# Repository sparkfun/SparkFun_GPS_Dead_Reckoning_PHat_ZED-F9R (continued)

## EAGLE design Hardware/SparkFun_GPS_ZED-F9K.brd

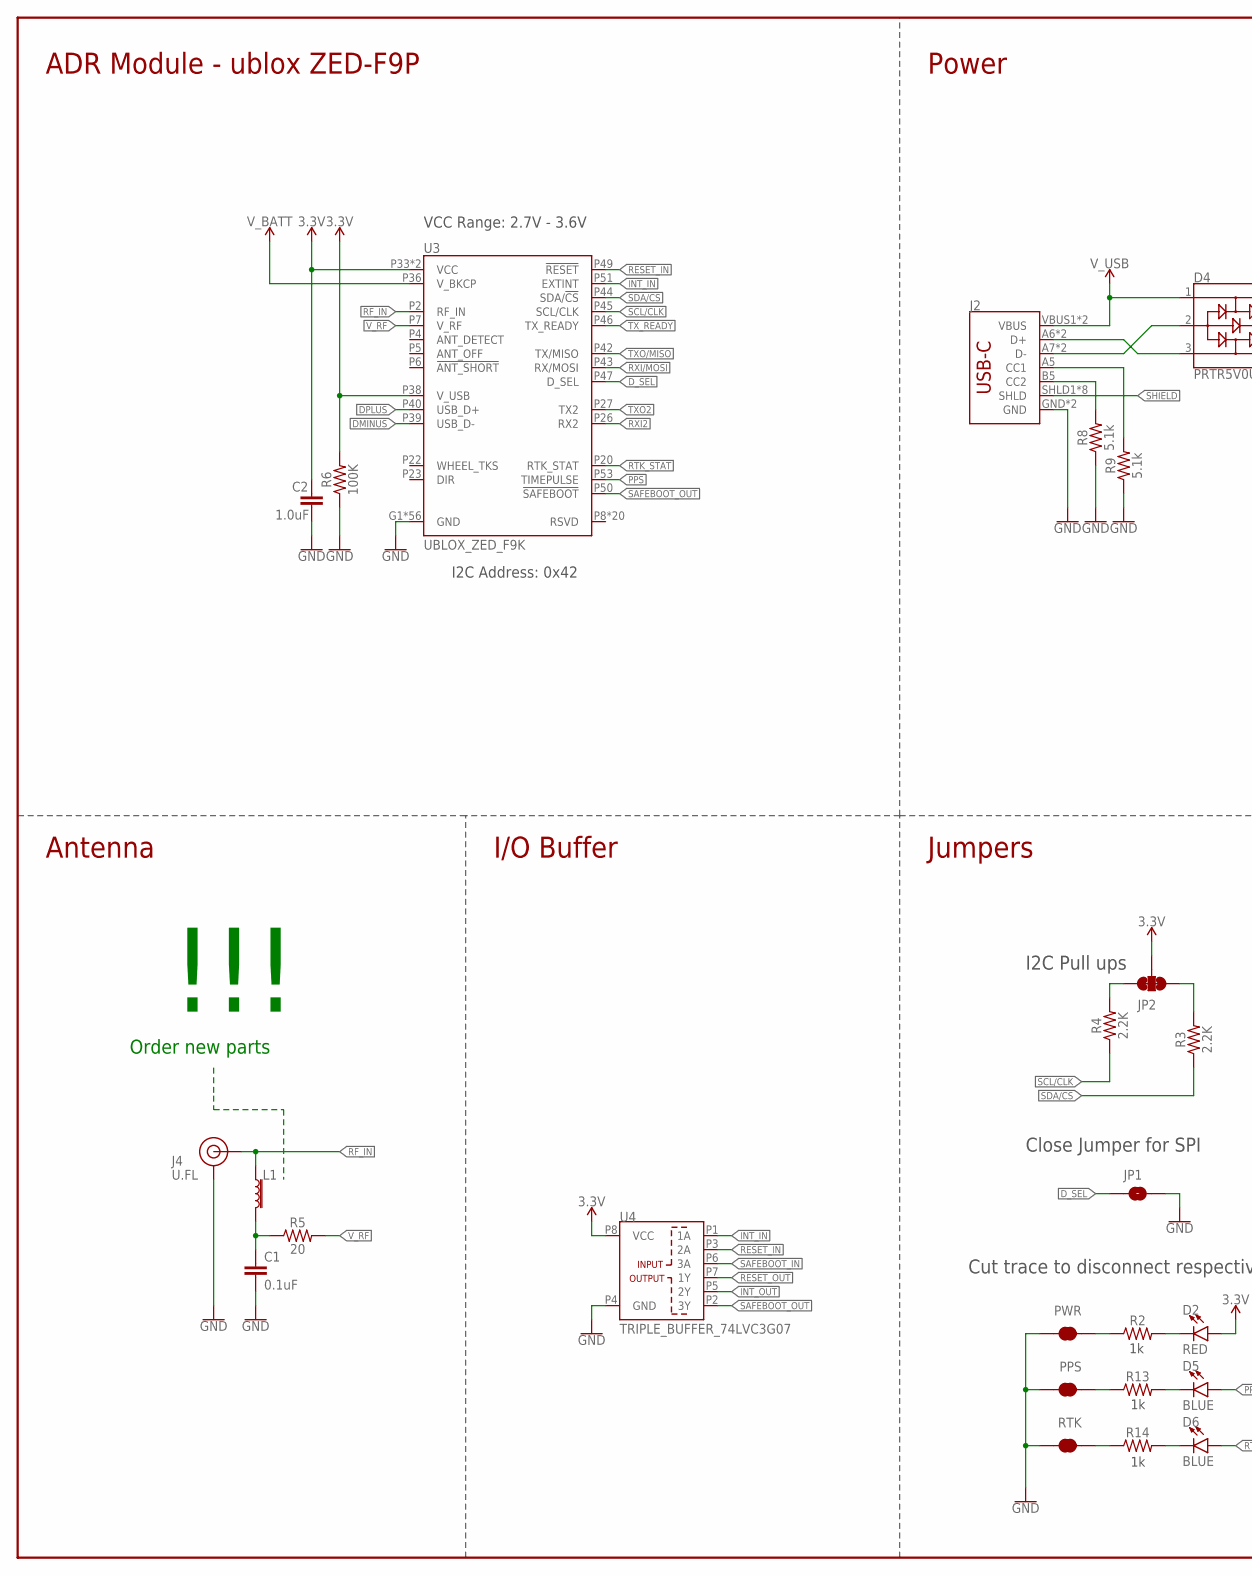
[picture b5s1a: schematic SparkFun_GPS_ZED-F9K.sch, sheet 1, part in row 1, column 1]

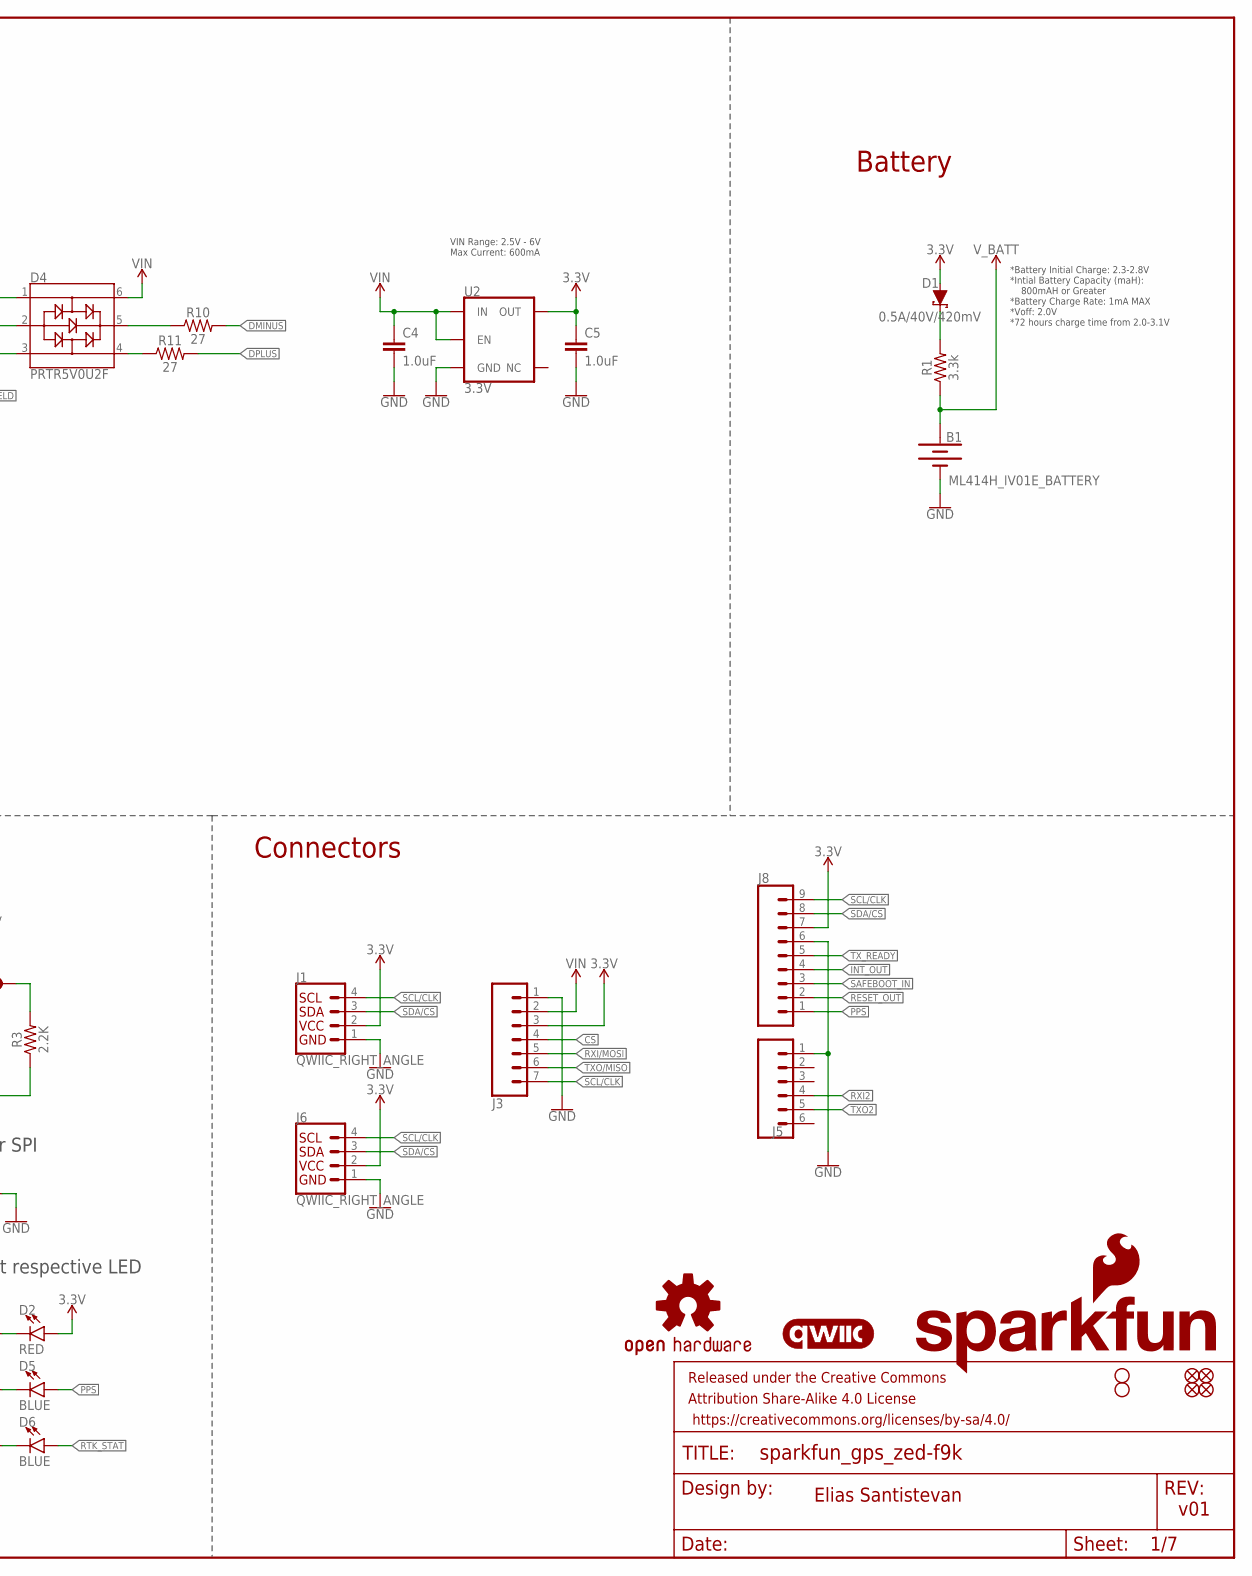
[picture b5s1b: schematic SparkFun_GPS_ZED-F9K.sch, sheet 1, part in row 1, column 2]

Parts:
B1: ML414H_IV01E_BATTERY; ML414H_IV01E
C1: 0.1uF; 0402
C2: 1.0uF; 0402
C4, C5: 1.0uF; 0603
D1: 0.5A/40V/420mV; SOD-323
D2: RED; LED-0603
D4: PRTR5V0U2F; SOT886
D5, D6: BLUE; LED-0603
FD1, FD2, FD3, FD4: FIDUCIALUFIDUCIAL; FIDUCIAL-MICRO
FRAME2: FRAME-LEDGER; CREATIVE_COMMONS
H2, H3: STAND-OFFTIGHT; STAND-OFF-TIGHT
J1, J6: QWIIC_RIGHT_ANGLE; JST04_1MM_RA
J2: USB_C2-LAYER; USB-C-16P
J3: CONN_07NO_SILK; 1X07_NO_SILK
J4: U.FL
J5: CONN_06NO_SILK_NO_POP; 1X06_NO_SILK
J8: CONN_09NO_SILK; 1X09_NO_SILK
JP1: JUMPER-SMT_2_NO_SILK; SMT-JUMPER_2_NO_SILK
JP2: JUMPER-SMT_3_2-NC_TRACE_SILK; SMT-JUMPER_3_2-NC_TRACE_SILK
L1: 3.9NH; 0402
LOGO1: SFE_LOGO_NAME_FLAME.2_INCH; SFE_LOGO_NAME_FLAME_.2
LOGO2: QWIIC_LOGO_4MM; QWIIC_4MM
LOGO3: OSHW-LOGOM; OSHW-LOGO-M
PPS: JUMPER-SMT_2_NC_TRACE_SILK; SMT-JUMPER_2_NC_TRACE_SILK
PWR: JUMPER-SMT_2_NC_TRACE_SILK; SMT-JUMPER_2_NC_TRACE_SILK
R1: 3.3k; 0603
R2, R13, R14: 1KOHM-0402-1/16W-1%; 0402
R3, R4: 2.2K; 0402
R5: 20; 0603
R6: 100K; 0402
R8, R9: 5.1k; 0402
R10, R11: 27; 0603
RTK: JUMPER-SMT_2_NC_TRACE_SILK; SMT-JUMPER_2_NC_TRACE_SILK
U2: 3.3V; SOT23-5
U3: UBLOX_ZED_F9K
U4: TRIPLE_BUFFER_74LVC3G07; SOP_8-PIN

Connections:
3.3V: C2.1, C5.1, D1.A, D2.A, J1.2, J3.3, J6.2, J8.7, JP2.2, R6.2, U2.5 (OUT), U3.P33 (VCC), U3.P34 (VCC), U3.P38 (V_USB), U4.P8 (VCC)
!CS: J3.4
!RESET_IN: U3.P49 (!RESET!), U4.P3 (2A)
!RESET_OUT: J8.2, U4.P7 (1Y)
!SAFEBOOT_IN: J8.3, U4.P6 (3A)
!SAFEBOOT_OUT: U3.P50 (!SAFEBOOT!), U4.P2 (3Y)
DMINUS: R10.2, U3.P39 (USB_D-)
DPLUS: R11.2, U3.P40 (USB_D+)
D_SEL: JP1.1, U3.P47 (D_SEL)
GND: B1.-, C1.2, C2.2, C4.2, C5.2, J1.1, J2.GND, J2.GND2 (GND), J3.1, J4.1 (GND), J4.2 (GND), J5.1, J6.1, J8.6, JP1.2, PPS.1, PWR.1, R6.1, R8.1, R9.1, RTK.1, U2.2 (GND), U3.G1 (GND), U3.G2 (GND), U3.G3 (GND), U3.G4 (GND), U3.G5 (GND), U3.G6 (GND), U3.G7 (GND), U3.G8 (GND), U3.G9 (GND), U3.G10 (GND), U3.G11 (GND), U3.G12 (GND), U3.G13 (GND), U3.G14 (GND), U3.G15 (GND), U3.G16 (GND), U3.G17 (GND), U3.G18 (GND), U3.G19 (GND), U3.G20 (GND), U3.G21 (GND), U3.G22 (GND), U3.G23 (GND), U3.G24 (GND), U3.G25 (GND), U3.G26 (GND), U3.G27 (GND), U3.G28 (GND), U3.G29 (GND), U3.G30 (GND), U3.G31 (GND), U3.G32 (GND), U3.G33 (GND), U3.G34 (GND), U3.G35 (GND), U3.G36 (GND), U3.G37 (GND), U3.G38 (GND), U3.G39 (GND), U3.G40 (GND), U3.G41 (GND), U3.G42 (GND), U3.G43 (GND), U3.G44 (GND), U3.G45 (GND), U3.G46 (GND), U3.G47 (GND), U3.G48 (GND), U3.P1 (GND), U3.P3 (GND), U3.P12 (GND), U3.P14 (GND), U3.P32 (GND), U3.P37 (GND), U3.P41 (GND), U3.P48 (GND), U4.P4 (GND)
INT_IN: U3.P51 (EXTINT), U4.P1 (1A)
INT_OUT: J8.4, U4.P5 (2Y)
unnamed: JP2.1, R3.2
unnamed: D1.C, R1.2
unnamed: JP2.3, R4.2
unnamed: D2.C, R2.2
unnamed: C1.1, L1.2, R5.1
unnamed: D4.3, J2.A6 (D+), J2.B6 (D+)
unnamed: D4.2, J2.A7 (D-), J2.B7 (D-)
unnamed: PWR.2, R2.1
unnamed: J2.B5 (CC2), R8.2
unnamed: J2.A5 (CC1), R9.2
unnamed: D4.5, R10.1
unnamed: D4.4, R11.1
unnamed: R14.1, RTK.2
unnamed: PPS.2, R13.1
unnamed: D5.C, R13.2
unnamed: D6.C, R14.2
PPS: D5.A, J8.1, U3.P53 (TIMEPULSE)
RF_IN: J4.FEED (SIGNAL), L1.1, U3.P2 (RF_IN)
RTK_STAT: D6.A, U3.P20 (RTK_STAT)
RXI2: J5.4, U3.P26 (RX2)
RXI/MOSI: J3.5, U3.P43 (RX/MOSI)
SCL/CLK: J1.4, J3.7, J6.4, J8.9, R4.1, U3.P45 (SCL/CLK)
SDA/!CS: J1.3, J6.3, J8.8, R3.1, U3.P44 (SDA/!CS!)
SHIELD: J2.SHLD1 (SHLD), J2.SHLD2 (SHLD), J2.SHLD3 (SHLD), J2.SHLD4 (SHLD), J2.SHLD5 (SHLD), J2.SHLD6 (SHLD), J2.SHLD7 (SHLD), J2.SHLD8 (SHLD)
TXO2: J5.5, U3.P27 (TX2)
TXO/MISO: J3.6, U3.P42 (TX/MISO)
TX_READY: J8.5, U3.P46 (TX_READY)
VIN: C4.1, D4.6, J3.2, U2.1 (IN), U2.3 (EN)
V_BATT: B1.+, R1.1, U3.P36 (V_BKCP)
V_RF: R5.2, U3.P7 (V_RF)
V_USB: D4.1, J2.VBUS1 (VBUS), J2.VBUS2 (VBUS)

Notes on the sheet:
v01
Elias Santistevan
ADR Module - ublox ZED-F9P
Battery
Connectors
Jumpers
Close Jumper for SPI
I2C Pull ups
Cut trace to disconnect respective LED
Antenna
*Battery Initial Charge: 2.3-2.8V *Intial Battery Capacity (maH): 800mAH or Greater *Battery Charge Rate: 1mA MAX *Voff: 2.0V *72 hours charge time from 2.0-3.1V
Order new parts
!!!
VIN Range: 2.5V - 6V Max Current: 600mA
Power
I/O Buffer
VCC Range: 2.7V - 3.6V
I2C Address: 0x42

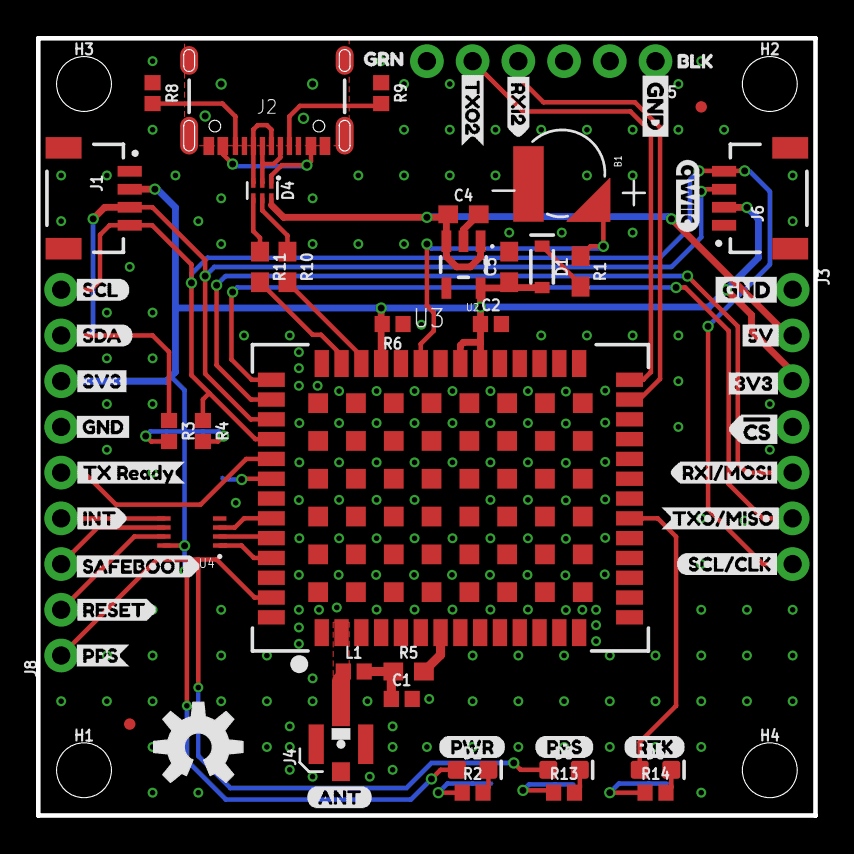
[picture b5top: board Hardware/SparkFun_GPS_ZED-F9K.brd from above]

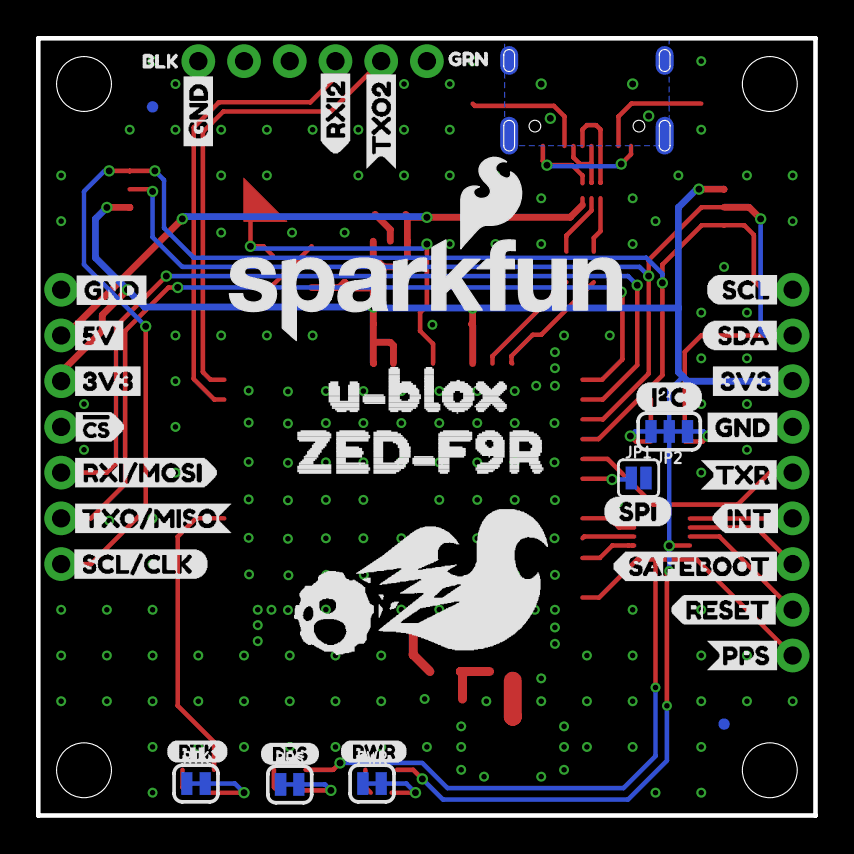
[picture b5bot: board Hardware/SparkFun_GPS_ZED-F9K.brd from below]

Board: 2 copper layers, 43.2 x 43.2 mm, 104 parts (37 on the bottom side), 42 nets.

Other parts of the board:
H1, H4: STAND-OFFTIGHT; STAND-OFF-TIGHT
U$1, U$24: INT2
U$2: PPS4
U$3, U$19: 3V32
U$4, U$47: PPS8
U$5, U$48: PWR10
U$6: GND3
U$7: RESET3
U$8, U$22: RTK9
U$9: RXI#MOSI5
U$10: SAFEBOOT1
U$11: SCL0
U$12: SDA1
U$13: SCL#CLK7
U$14: RXI22
U$15: TXO#MISO6
U$16: TX_READY0
U$17, U$20: GND-03
U$18: 5V0
U$21, U$54: BLK2
U$23, U$53: GRN1
U$25, U$36: TXO21
U$26: CS#-<]-04
U$27: PPS1
U$28: RESET4
U$29, U$40: 3V3-04
U$30: RXI#MOSI0
U$31, U$34, U$41: GND-04
U$32: SAFEBOOT3
U$33: 5V
U$35: RXI28
U$37: TXO#MISO1
U$38: SCL#CLK2
U$39: SCL5
U$42: SDA4
U$43: TXR3
U$45: SPI4
U$46: I_SUPER2_C-()-04
U$49: ANT0
U$50: NEO_GPS_BOARD_SILK_FINAL#03#JPG
U$51: ZED#F9R0
U$52: U#BLOX1
U$59: CS#-[>-04

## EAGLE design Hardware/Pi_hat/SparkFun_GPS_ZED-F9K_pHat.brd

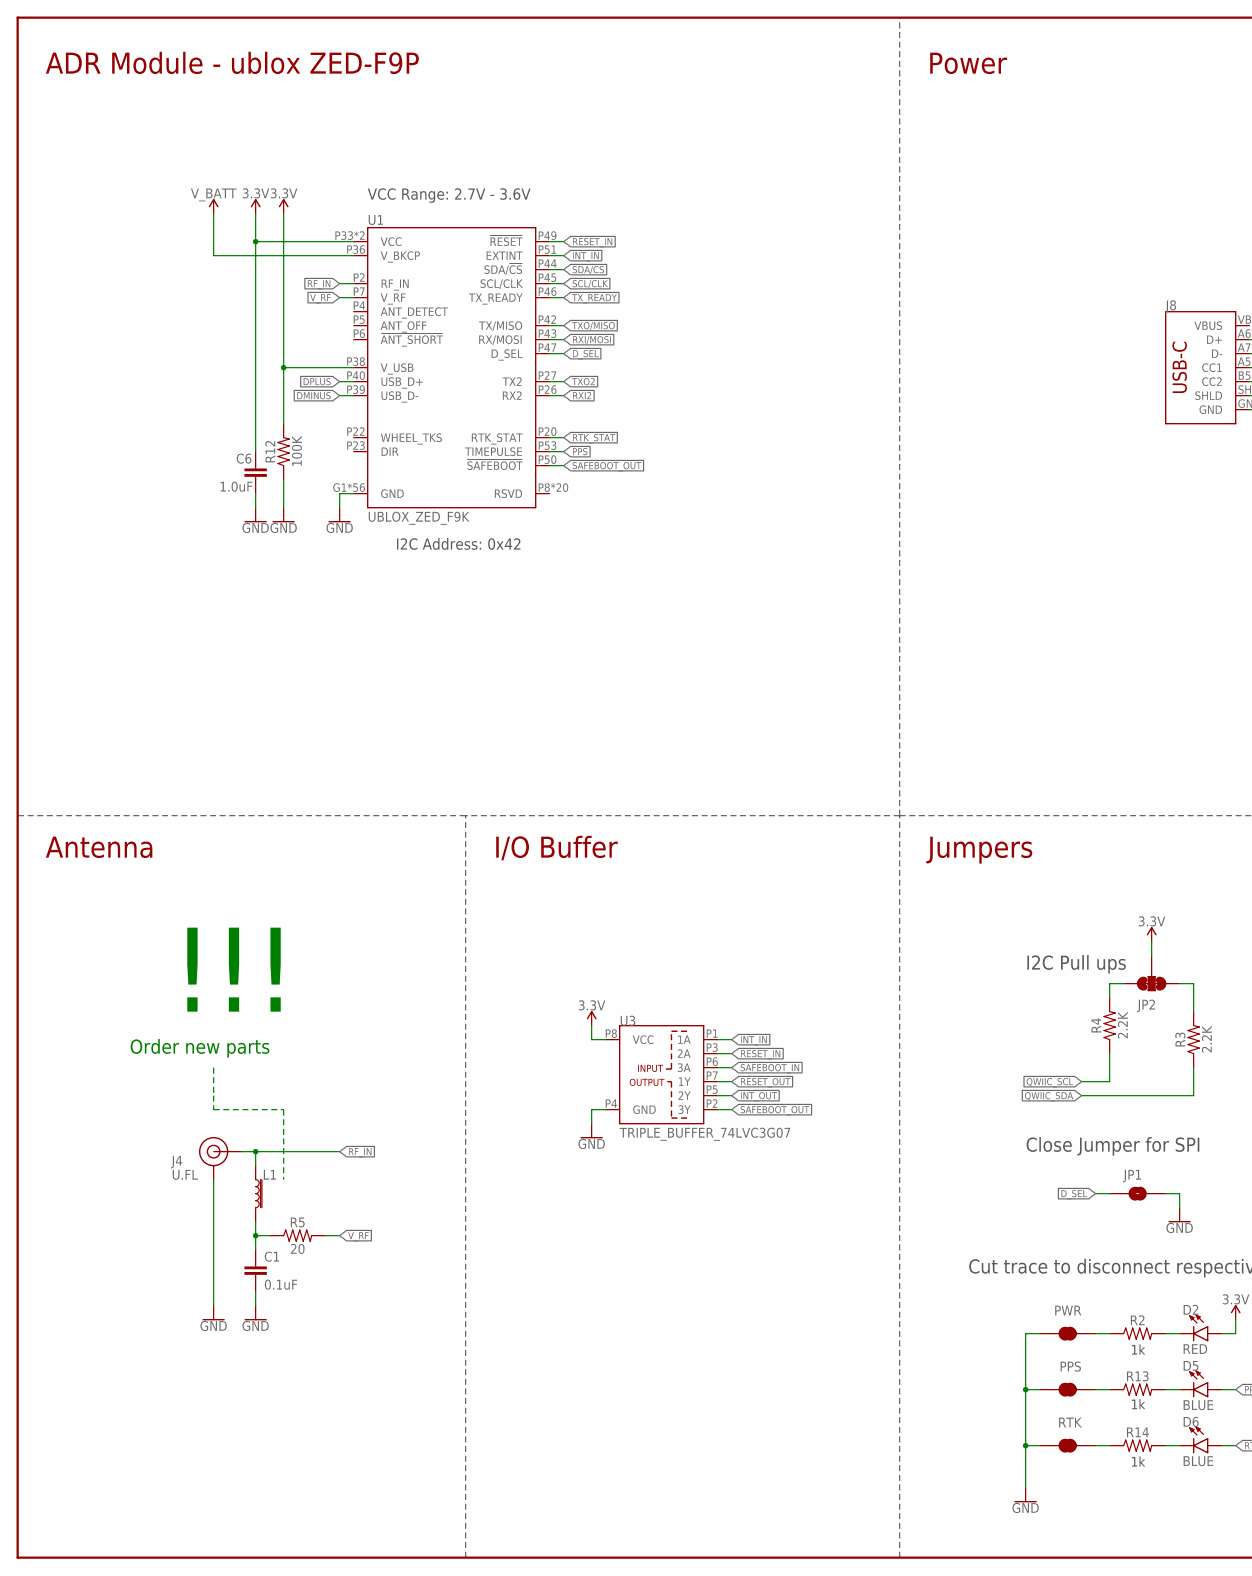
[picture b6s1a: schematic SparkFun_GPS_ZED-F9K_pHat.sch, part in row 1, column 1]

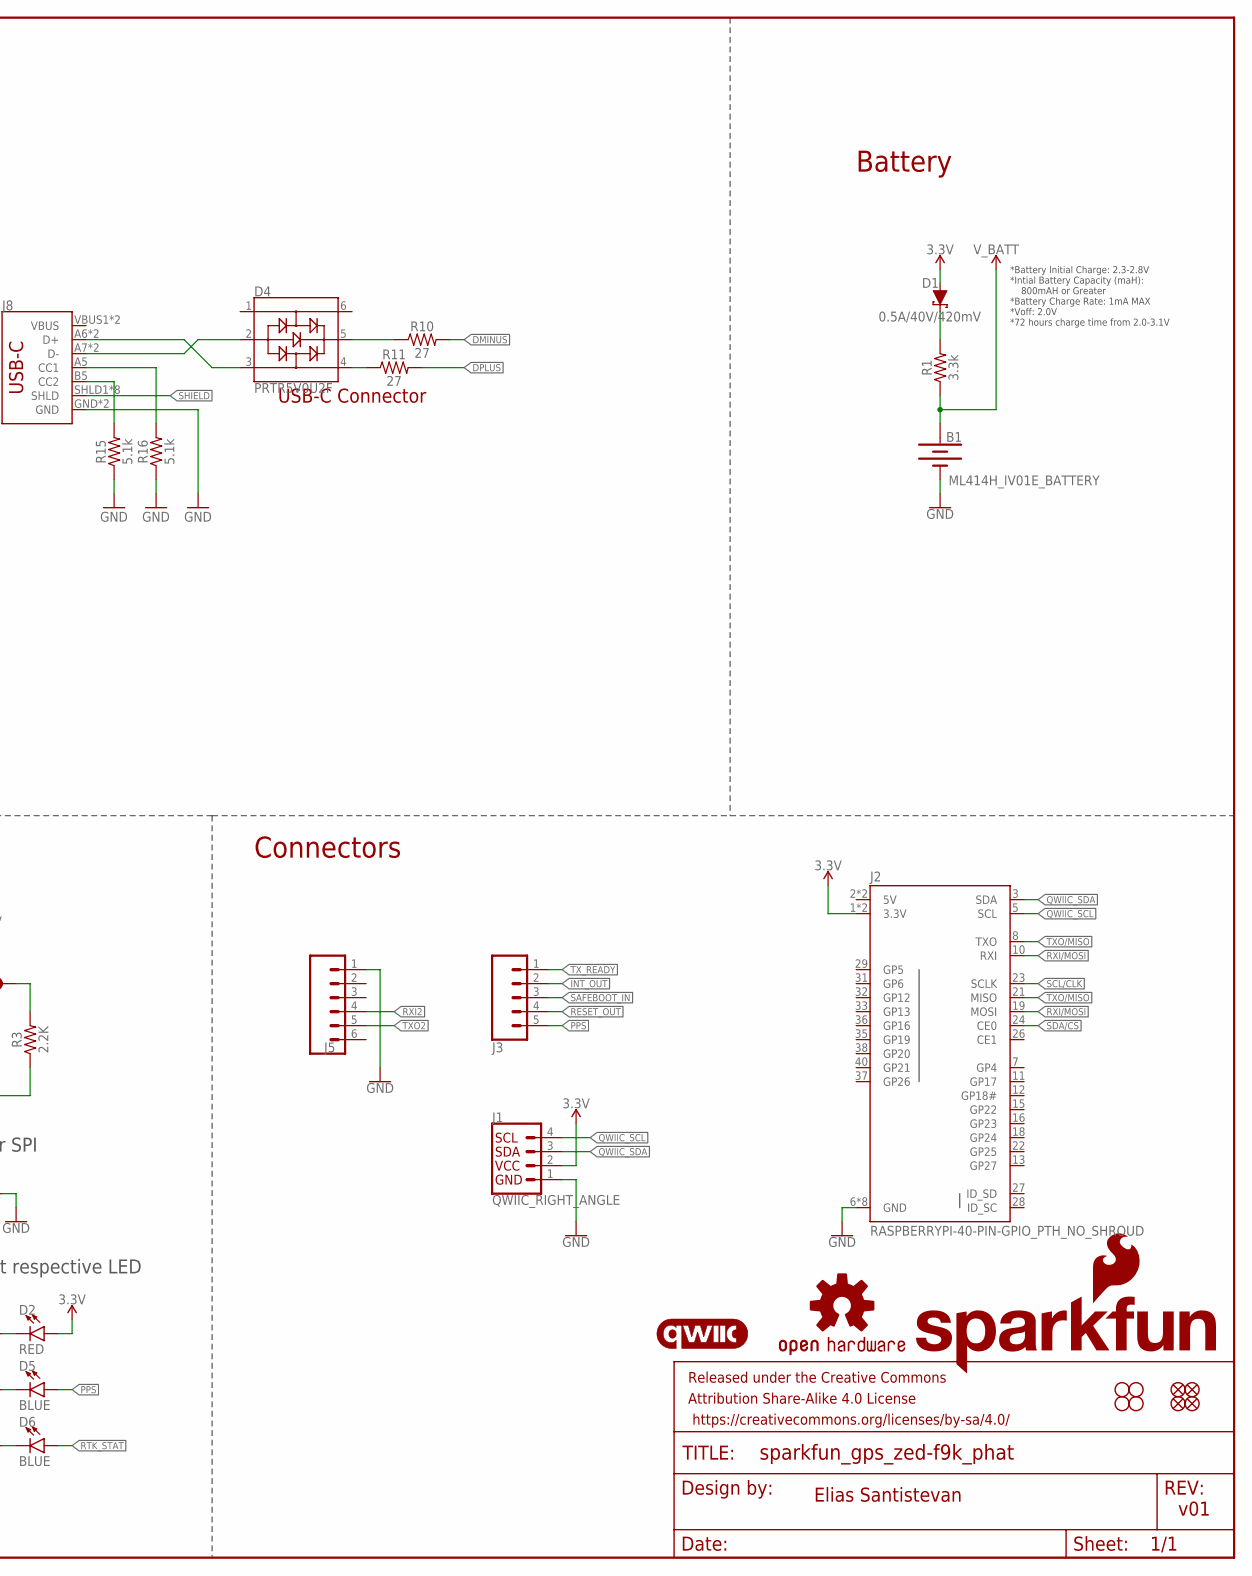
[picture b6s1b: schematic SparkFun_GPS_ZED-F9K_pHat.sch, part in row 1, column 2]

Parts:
B1: ML414H_IV01E_BATTERY; ML414H_IV01E
C1: 0.1uF; 0402
C6: 1.0uF; 0402
D1: 0.5A/40V/420mV; SOD-323
D2: RED; LED-0603
D4: PRTR5V0U2F; SOT886
D5, D6: BLUE; LED-0603
FD9, FD10, FD11, FD12: FIDUCIALUFIDUCIAL; FIDUCIAL-MICRO
FRAME2: FRAME-LEDGER; CREATIVE_COMMONS
H9, H10, H11, H12: STAND-OFFTIGHT; STAND-OFF-TIGHT
J1: QWIIC_RIGHT_ANGLE; JST04_1MM_RA
J2: RASPBERRYPI-40-PIN-GPIO_PTH_NO_SHROUD; 2X20
J3: CONN_05NO_SILK; 1X05_NO_SILK
J4: U.FL
J5: CONN_06NO_SILK_NO_POP; 1X06_NO_SILK
J8: USB_C2-LAYER; USB-C-16P
JP1: JUMPER-SMT_2_NO_SILK; SMT-JUMPER_2_NO_SILK
JP2: JUMPER-SMT_3_2-NC_TRACE_SILK; SMT-JUMPER_3_2-NC_TRACE_SILK
L1: 3.9NH; 0402
LOGO1: SFE_LOGO_NAME_FLAME.2_INCH; SFE_LOGO_NAME_FLAME_.2
LOGO2: OSHW-LOGOM; OSHW-LOGO-M
LOGO3: QWIIC_LOGO_5MM; QWIIC_5MM
PPS: JUMPER-SMT_2_NC_TRACE_SILK; SMT-JUMPER_2_NC_TRACE_SILK
PWR: JUMPER-SMT_2_NC_TRACE_SILK; SMT-JUMPER_2_NC_TRACE_SILK
R1: 3.3k; 0603
R2, R13, R14: 1KOHM-0402-1/16W-1%; 0402
R3, R4: 2.2K; 0402
R5: 20; 0603
R10, R11: 27; 0603
R12: 100K; 0402
R15, R16: 5.1k; 0402
RTK: JUMPER-SMT_2_NC_TRACE_SILK; SMT-JUMPER_2_NC_TRACE_SILK
U1: UBLOX_ZED_F9K
U3: TRIPLE_BUFFER_74LVC3G07; SOP_8-PIN

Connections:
3.3V: C6.1, D1.A, D2.A, J1.2, J2.1 (3.3V), J2.17 (3.3V), JP2.2, R12.2, U1.P33 (VCC), U1.P34 (VCC), U1.P38 (V_USB), U3.P8 (VCC)
5V: J2.2 (5V), J2.4 (5V)
!RESET_IN: U1.P49 (!RESET!), U3.P3 (2A)
!RESET_OUT: J3.4, U3.P7 (1Y)
!SAFEBOOT_IN: J3.3, U3.P6 (3A)
!SAFEBOOT_OUT: U1.P50 (!SAFEBOOT!), U3.P2 (3Y)
DMINUS: R10.2, U1.P39 (USB_D-)
DPLUS: R11.2, U1.P40 (USB_D+)
D_SEL: JP1.1, U1.P47 (D_SEL)
GND: B1.-, C1.2, C6.2, J1.1, J2.6 (GND), J2.9 (GND), J2.14 (GND), J2.20 (GND), J2.25 (GND), J2.30 (GND), J2.34 (GND), J2.39 (GND), J4.1 (GND), J4.2 (GND), J5.1, J8.GND, J8.GND2 (GND), JP1.2, PPS.1, PWR.1, R12.1, R15.1, R16.1, RTK.1, U1.G1 (GND), U1.G2 (GND), U1.G3 (GND), U1.G4 (GND), U1.G5 (GND), U1.G6 (GND), U1.G7 (GND), U1.G8 (GND), U1.G9 (GND), U1.G10 (GND), U1.G11 (GND), U1.G12 (GND), U1.G13 (GND), U1.G14 (GND), U1.G15 (GND), U1.G16 (GND), U1.G17 (GND), U1.G18 (GND), U1.G19 (GND), U1.G20 (GND), U1.G21 (GND), U1.G22 (GND), U1.G23 (GND), U1.G24 (GND), U1.G25 (GND), U1.G26 (GND), U1.G27 (GND), U1.G28 (GND), U1.G29 (GND), U1.G30 (GND), U1.G31 (GND), U1.G32 (GND), U1.G33 (GND), U1.G34 (GND), U1.G35 (GND), U1.G36 (GND), U1.G37 (GND), U1.G38 (GND), U1.G39 (GND), U1.G40 (GND), U1.G41 (GND), U1.G42 (GND), U1.G43 (GND), U1.G44 (GND), U1.G45 (GND), U1.G46 (GND), U1.G47 (GND), U1.G48 (GND), U1.P1 (GND), U1.P3 (GND), U1.P12 (GND), U1.P14 (GND), U1.P32 (GND), U1.P37 (GND), U1.P41 (GND), U1.P48 (GND), U3.P4 (GND)
INT_IN: U1.P51 (EXTINT), U3.P1 (1A)
INT_OUT: J3.2, U3.P5 (2Y)
unnamed: JP2.1, R3.2
unnamed: D1.C, R1.2
unnamed: JP2.3, R4.2
unnamed: D2.C, R2.2
unnamed: C1.1, L1.2, R5.1
unnamed: PWR.2, R2.1
unnamed: J8.B5 (CC2), R15.2
unnamed: D4.5, R10.1
unnamed: D4.4, R11.1
unnamed: J8.A5 (CC1), R16.2
unnamed: R14.1, RTK.2
unnamed: PPS.2, R13.1
unnamed: D5.C, R13.2
unnamed: D6.C, R14.2
PPS: D5.A, J3.5, U1.P53 (TIMEPULSE)
QWIIC_SCL: J1.4, J2.5 (SCL), R4.1
QWIIC_SDA: J1.3, J2.3 (SDA), R3.1
RF_IN: J4.FEED (SIGNAL), L1.1, U1.P2 (RF_IN)
RTK_STAT: D6.A, U1.P20 (RTK_STAT)
RXI2: J5.4, U1.P26 (RX2)
RXI/MOSI: J2.10 (RXI), J2.19 (MOSI), U1.P43 (RX/MOSI)
SCL/CLK: J2.23 (SCLK), U1.P45 (SCL/CLK)
SDA/!CS: J2.24 (CE0), U1.P44 (SDA/!CS!)
SHIELD: J8.SHLD1 (SHLD), J8.SHLD2 (SHLD), J8.SHLD3 (SHLD), J8.SHLD4 (SHLD), J8.SHLD5 (SHLD), J8.SHLD6 (SHLD), J8.SHLD7 (SHLD), J8.SHLD8 (SHLD)
TXO2: J5.5, U1.P27 (TX2)
TXO/MISO: J2.8 (TXO), J2.21 (MISO), U1.P42 (TX/MISO)
TX_READY: J3.1, U1.P46 (TX_READY)
USB_D+: D4.3, J8.A6 (D+), J8.B6 (D+)
USB_D-: D4.2, J8.A7 (D-), J8.B7 (D-)
V_BATT: B1.+, R1.1, U1.P36 (V_BKCP)
V_RF: R5.2, U1.P7 (V_RF)

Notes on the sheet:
v01
Elias Santistevan
ADR Module - ublox ZED-F9P
Battery
Connectors
Jumpers
Close Jumper for SPI
I2C Pull ups
Cut trace to disconnect respective LED
Antenna
*Battery Initial Charge: 2.3-2.8V *Intial Battery Capacity (maH): 800mAH or Greater *Battery Charge Rate: 1mA MAX *Voff: 2.0V *72 hours charge time from 2.0-3.1V
VCC Range: 2.7V - 3.6V
I2C Address: 0x42
Order new parts
!!!
Power
I/O Buffer
USB-C Connector

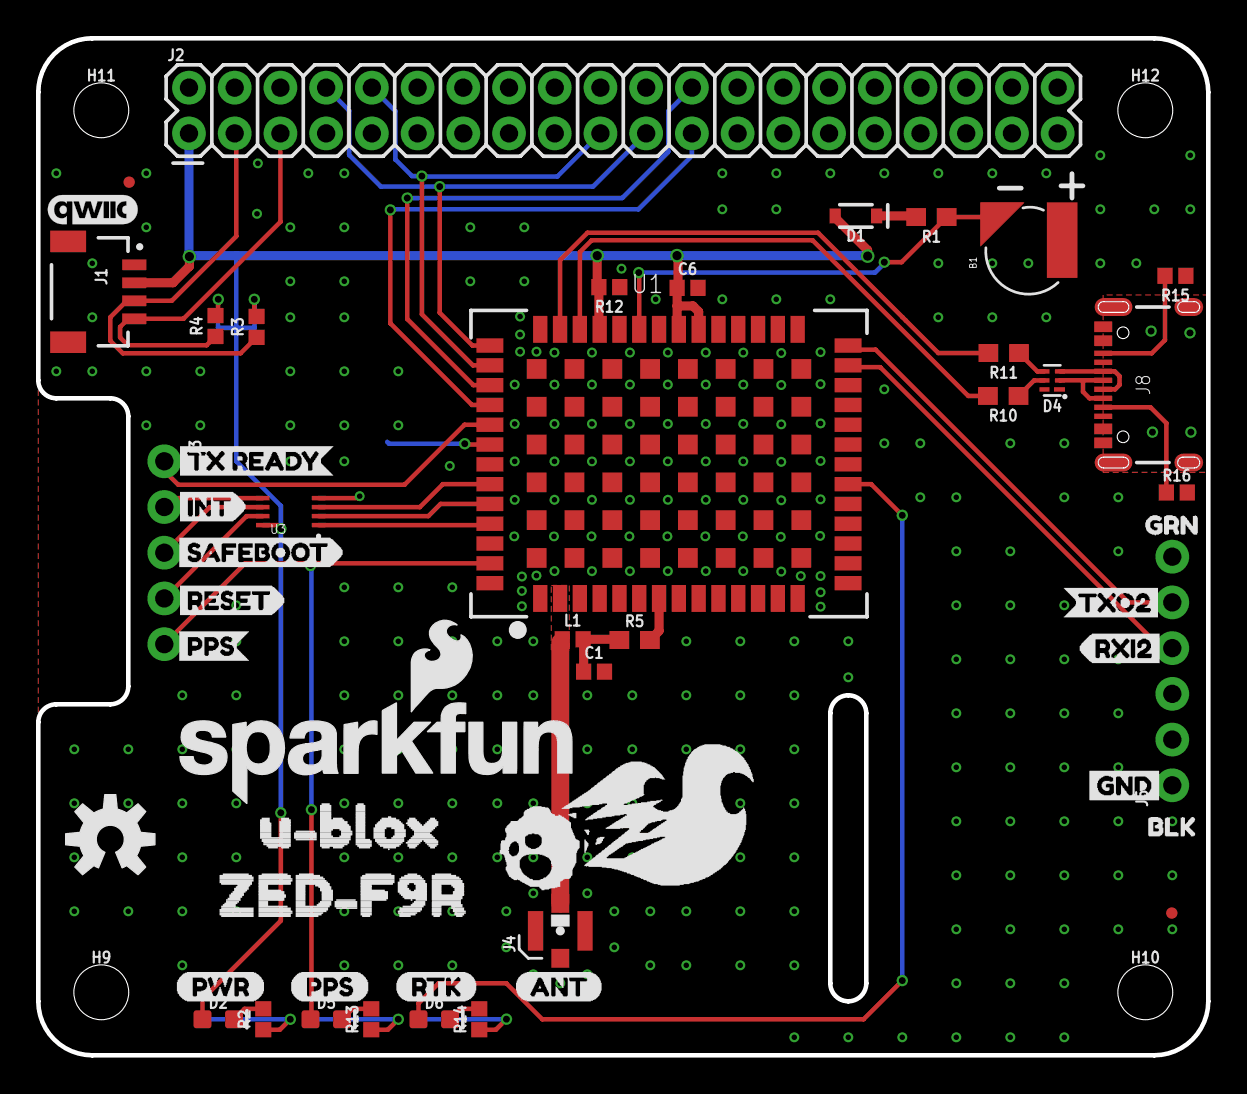
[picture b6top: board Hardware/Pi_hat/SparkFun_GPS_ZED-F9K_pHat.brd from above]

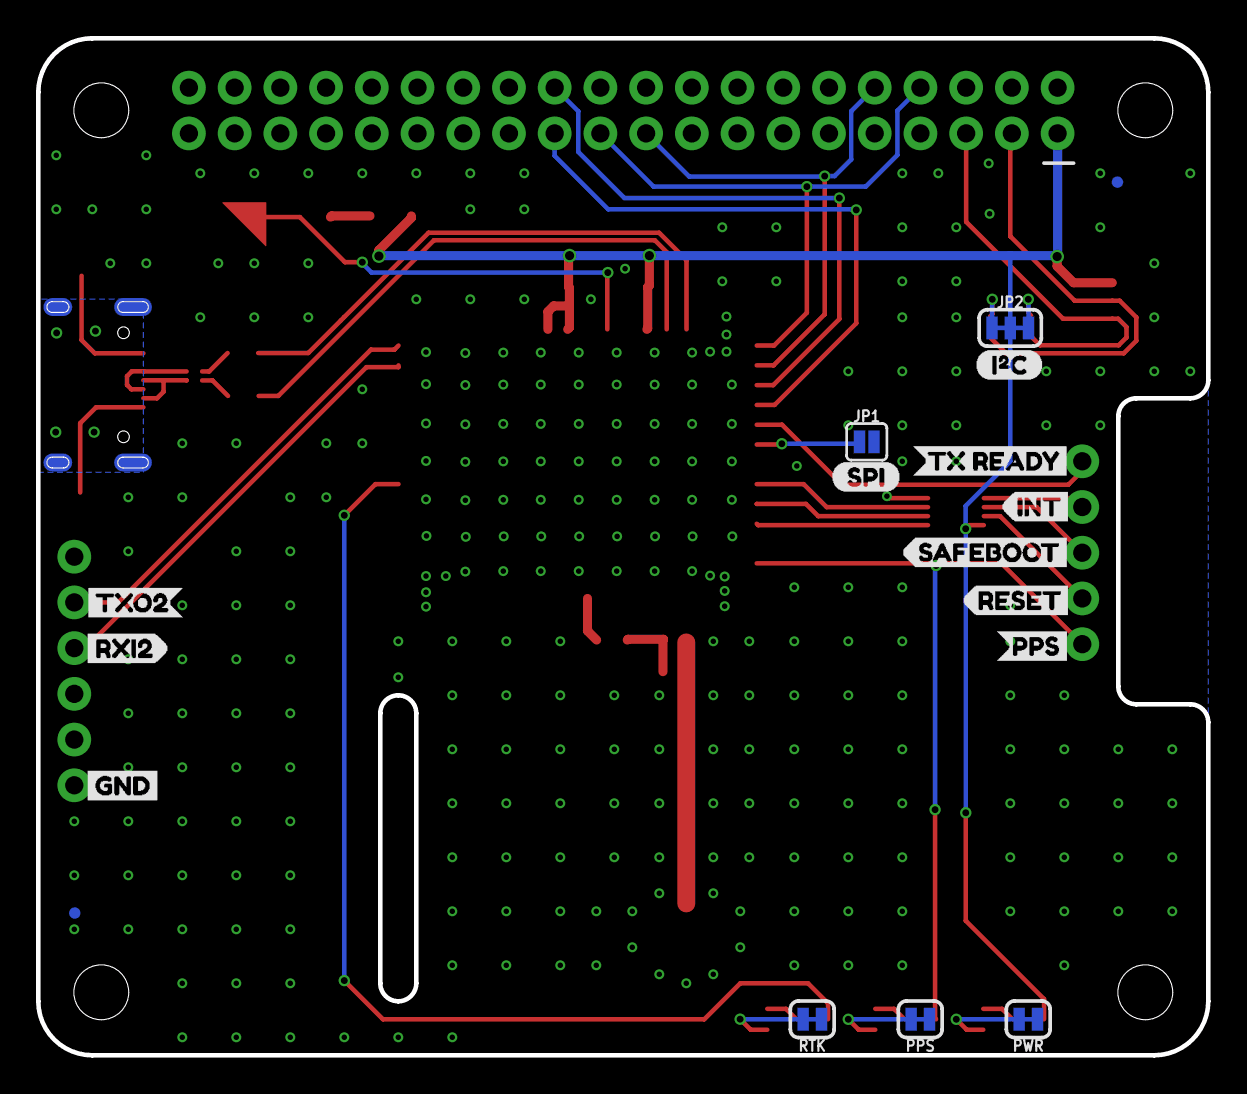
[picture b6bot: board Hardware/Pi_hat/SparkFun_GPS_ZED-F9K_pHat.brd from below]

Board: 2 copper layers, 65.0 x 56.5 mm, 73 parts (17 on the bottom side), 43 nets.

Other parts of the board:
U$1: INT1
U$2: PPS4
U$3: PPS6
U$4: PWR7
U$5: RTK5
U$6: RXI28
U$7: SAFEBOOT2
U$8: RESET0
U$9, U$17: TX_READY0
U$10: TXO21
U$11: INT2
U$12: PPS1
U$13: RESET4
U$14: RXI26
U$15: SAFEBOOT3
U$16: TXO25
U$18, U$19: GND-04
U$20: I_SUPER2_C-()-04
U$21: ANT1
U$22: BLK3
U$23: GRN2
U$24: SPI0
U$25: U#BLOX1
U$26: ZED#F9R0
U$27: NEO_GPS_BOARD_SILK_FINAL#03#JPG
